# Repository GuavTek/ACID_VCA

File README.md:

Schematic and PCB renders can be found on [CADLAB.io](https://cadlab.io/project/29056/main/files)

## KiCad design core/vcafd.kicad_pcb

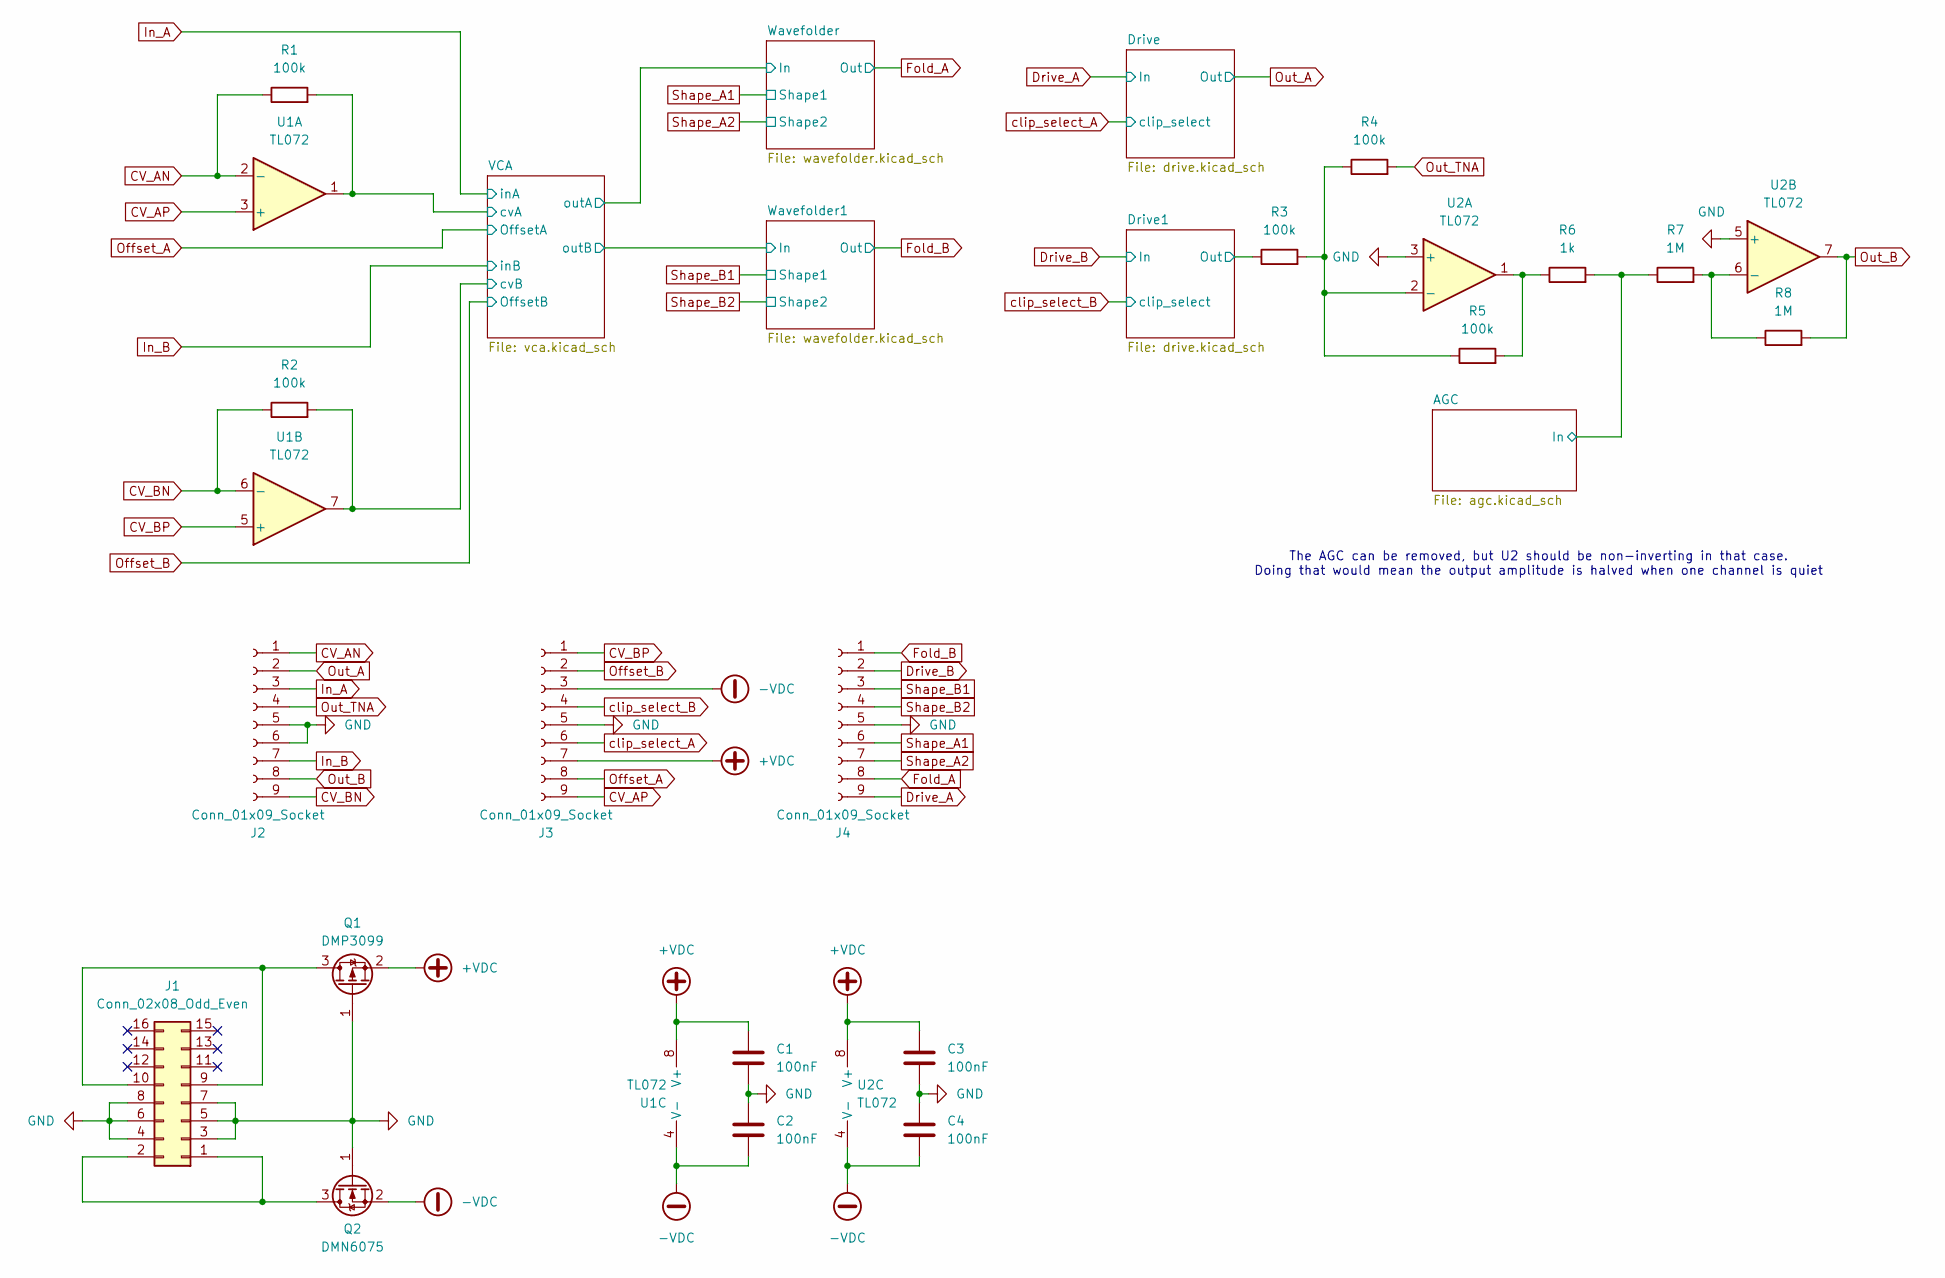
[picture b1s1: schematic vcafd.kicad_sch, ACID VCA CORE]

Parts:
C1, C2, C3, C4: 100nF; C_0603_1608Metric
J1: Conn_02x08_Odd_Even; Header_2x8_Shrouded_SMD
J2, J3, J4: Conn_01x09_Socket; PinSocket_1x09_P2.54mm_Vertical_SMD_Pin1Left
Q1: DMP3099; SOT-23
Q2: DMN6075; SOT-23
R1, R2, R3, R4, R5: 100k; R_0603_1608Metric
R6: 1k; R_0603_1608Metric
R7, R8: 1M; R_0603_1608Metric
U1, U2: TL072; SO-8_3.9x4.9mm_P1.27mm

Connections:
+VDC: C1.1, C3.1, J3.7, Q1.2 (S), U1.8 (V+), U2.8 (V+); also elsewhere on the board
-VDC: C2.2, C4.2, J3.3, Q2.2 (S), U1.4 (V-), U2.4 (V-); also elsewhere on the board
/AGC/In: R6.2, R7.1; also elsewhere on the board
/Drive1/Out: R3.1; also elsewhere on the board
/VCA/cvA: R1.2, U1.1; also elsewhere on the board
/VCA/cvB: R2.2, U1.7; also elsewhere on the board
CV_AN: J2.1, R1.1, U1.2 (-)
CV_AP: J3.9, U1.3 (+)
CV_BN: J2.9, R2.1, U1.6 (-)
CV_BP: J3.1, U1.5 (+)
Drive_A: J4.9; also elsewhere on the board
Drive_B: J4.2; also elsewhere on the board
Fold_A: J4.8; also elsewhere on the board
Fold_B: J4.1; also elsewhere on the board
GND: C1.2, C2.1, C3.2, C4.1, J1.3, J1.4, J1.5, J1.6, J1.7, J1.8, J2.5, J2.6, J3.5, J4.5, Q1.1 (G), Q2.1 (G), U2.3 (+), U2.5 (+); also elsewhere on the board
In_A: J2.3; also elsewhere on the board
In_B: J2.7; also elsewhere on the board
unnamed: J1.1, J1.2, Q2.3 (D)
unnamed: J1.9, J1.10, Q1.3 (D)
unnamed: R5.2, R6.1, U2.1
unnamed: R3.2, R4.1, R5.1, U2.2 (-)
unnamed: R7.2, R8.1, U2.6 (-)
Offset_A: J3.8; also elsewhere on the board
Offset_B: J3.2; also elsewhere on the board
Out_A: J2.2; also elsewhere on the board
Out_B: J2.8, R8.2, U2.7
Out_TNA: J2.4, R4.2
Shape_A1: J4.6; also elsewhere on the board
Shape_A2: J4.7; also elsewhere on the board
Shape_B1: J4.3; also elsewhere on the board
Shape_B2: J4.4; also elsewhere on the board
clip_select_A: J3.6; also elsewhere on the board
clip_select_B: J3.4; also elsewhere on the board

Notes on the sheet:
The AGC can be removed, but U2 should be non-inverting in that case. Doing that would mean the output amplitude is halved when one channel is quiet

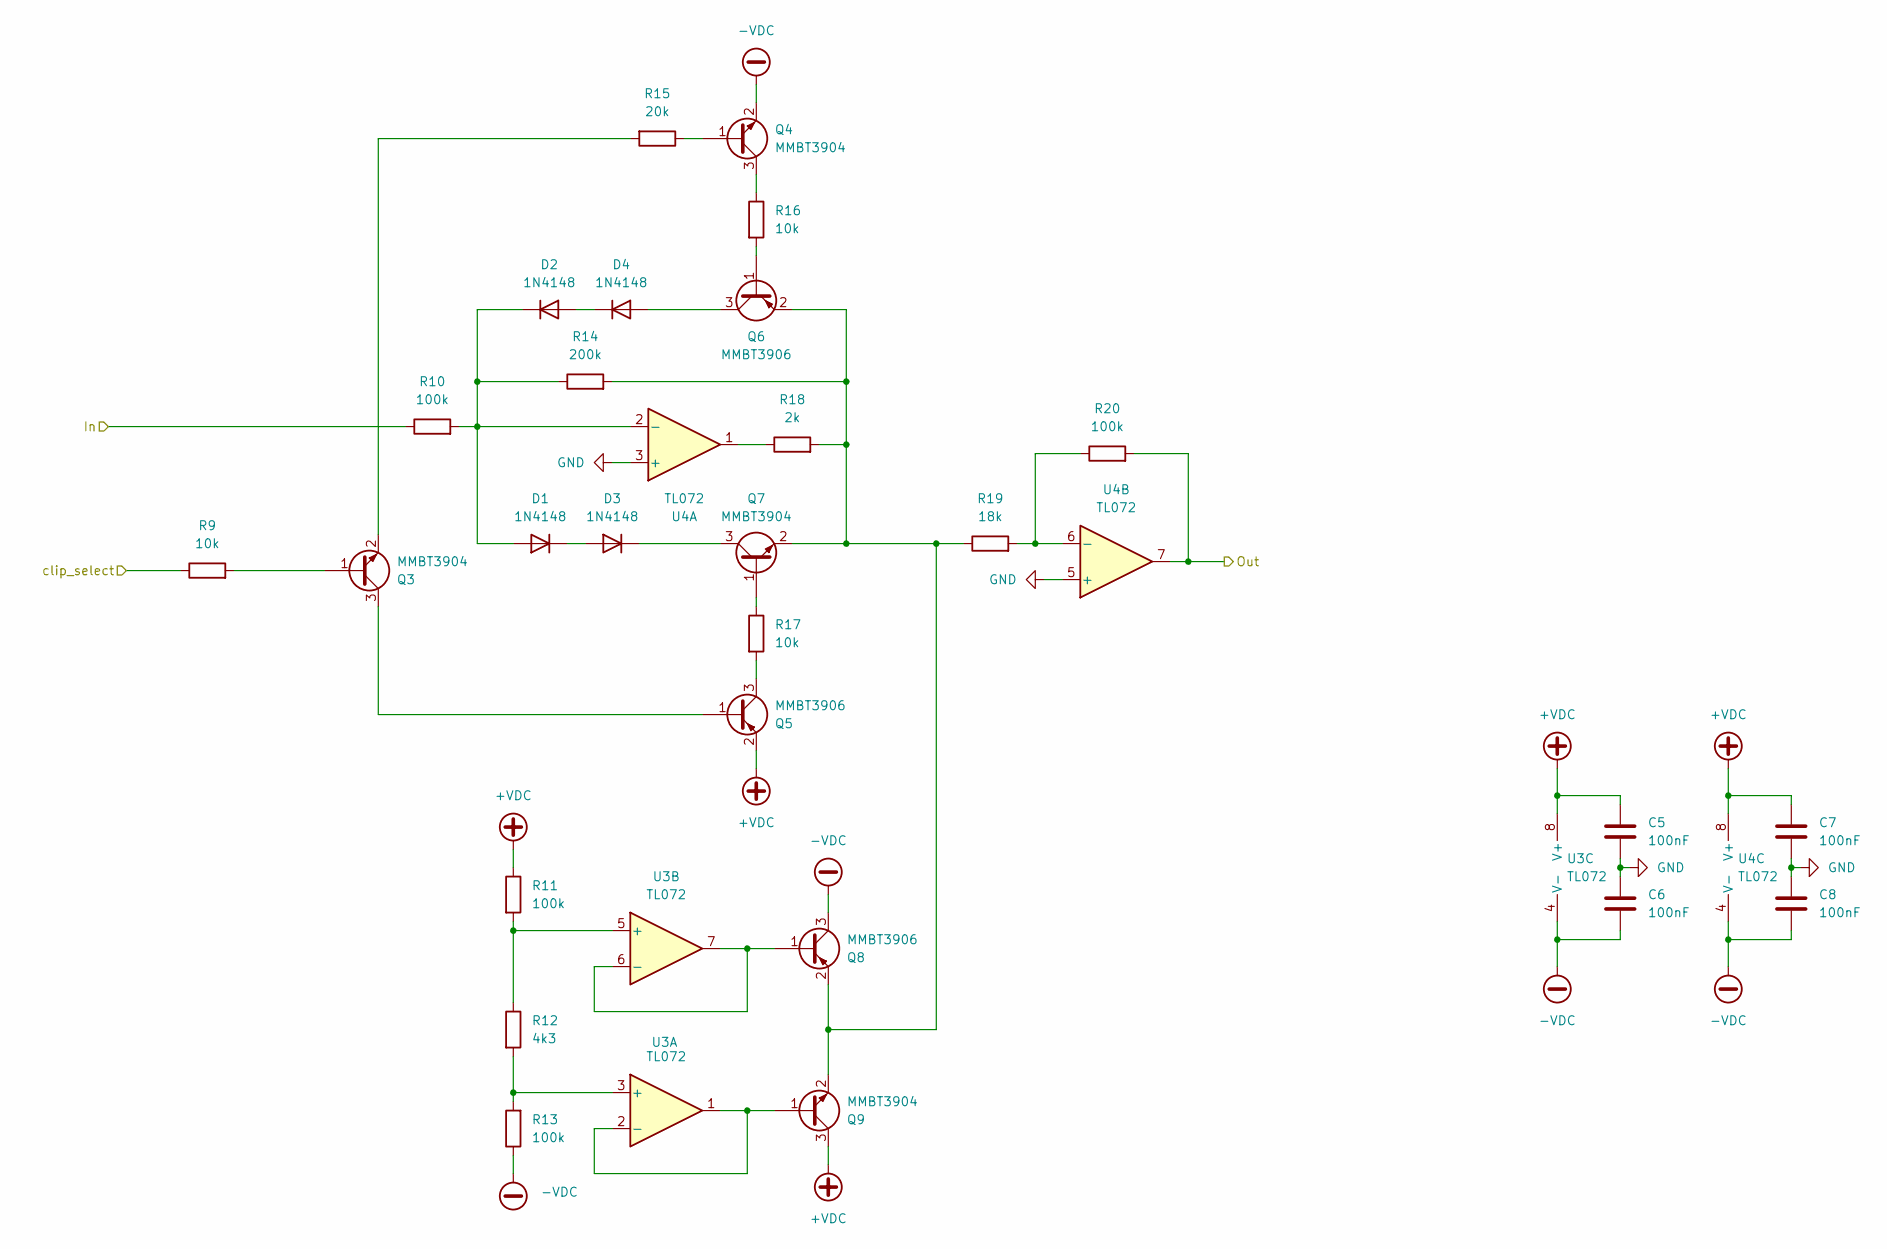
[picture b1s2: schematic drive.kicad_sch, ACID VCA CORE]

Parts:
C5, C6, C7, C8: 100nF; C_0603_1608Metric
D1, D2, D3, D4: 1N4148; D_SOD-323_HandSoldering
Q3, Q4, Q7, Q9: MMBT3904; SOT-23
Q5, Q6, Q8: MMBT3906; SOT-23
R9, R16, R17: 10k; R_0603_1608Metric
R10, R11, R13, R20: 100k; R_0603_1608Metric
R12: 4k3; R_0603_1608Metric
R14: 200k; R_0603_1608Metric
R15: 20k; R_0603_1608Metric
R18: 2k; R_0603_1608Metric
R19: 18k; R_0603_1608Metric
U3, U4: TL072; SO-8_3.9x4.9mm_P1.27mm

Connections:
+VDC: C5.1, C7.1, Q5.2 (E), Q9.3 (C), R11.1, U3.8 (V+), U4.8 (V+); also elsewhere on the board
-VDC: C6.2, C8.2, Q4.2 (E), Q8.3 (C), R13.1, U3.4 (V-), U4.4 (V-); also elsewhere on the board
/Drive1/Out: R20.2, U4.7; also elsewhere on the board
Drive_B: R10.1; also elsewhere on the board
GND: C5.2, C6.1, C7.2, C8.1, U4.3 (+), U4.5 (+); also elsewhere on the board
unnamed: D1.2 (A), D2.1 (K), R10.2, R14.1, U4.2 (-)
unnamed: D1.1 (K), D3.2 (A)
unnamed: D2.2 (A), D4.1 (K)
unnamed: D3.1 (K), Q7.3 (C)
unnamed: D4.2 (A), Q6.3 (C)
unnamed: Q3.1 (B), R9.2
unnamed: Q3.3 (C), Q5.1 (B)
unnamed: Q3.2 (E), R15.2
unnamed: Q4.1 (B), R15.1
unnamed: Q4.3 (C), R16.1
unnamed: Q5.3 (C), R17.2
unnamed: Q6.1 (B), R16.2
unnamed: Q6.2 (E), Q7.2 (E), Q8.2 (E), Q9.2 (E), R14.2, R18.2, R19.1
unnamed: Q7.1 (B), R17.1
unnamed: Q8.1 (B), U3.6 (-), U3.7
unnamed: Q9.1 (B), U3.1, U3.2 (-)
unnamed: R18.1, U4.1
unnamed: R12.2, R13.2, U3.3 (+)
unnamed: R11.2, R12.1, U3.5 (+)
unnamed: R19.2, R20.1, U4.6 (-)
clip_select_B: R9.1; also elsewhere on the board

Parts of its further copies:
C16, C17, C18, C19: 100nF; C_0603_1608Metric
D31, D32, D33, D34: 1N4148; D_SOD-323_HandSoldering
Q12, Q13, Q16, Q18: MMBT3904; SOT-23
Q14, Q15, Q17: MMBT3906; SOT-23
R55, R62, R63: 10k; R_0603_1608Metric
R56, R57, R59, R66: 100k; R_0603_1608Metric
R58: 4k3; R_0603_1608Metric
R60: 200k; R_0603_1608Metric
R61: 20k; R_0603_1608Metric
R64: 2k; R_0603_1608Metric
R65: 18k; R_0603_1608Metric
U8, U9: TL072; SO-8_3.9x4.9mm_P1.27mm

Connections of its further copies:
+VDC: C16.1, C18.1, Q14.2 (E), Q18.3 (C), R57.1, U8.8 (V+), U9.8 (V+); also elsewhere on the board
-VDC: C17.2, C19.2, Q13.2 (E), Q17.3 (C), R59.1, U8.4 (V-), U9.4 (V-); also elsewhere on the board
Drive_A: R56.1; also elsewhere on the board
GND: C16.2, C17.1, C18.2, C19.1, U9.3 (+), U9.5 (+); also elsewhere on the board
unnamed: D31.2 (A), D32.1 (K), R56.2, R60.1, U9.2 (-)
unnamed: D31.1 (K), D33.2 (A)
unnamed: D32.2 (A), D34.1 (K)
unnamed: D33.1 (K), Q16.3 (C)
unnamed: D34.2 (A), Q15.3 (C)
unnamed: Q12.1 (B), R55.2
unnamed: Q12.3 (C), Q14.1 (B)
unnamed: Q12.2 (E), R61.2
unnamed: Q13.1 (B), R61.1
unnamed: Q13.3 (C), R62.1
unnamed: Q14.3 (C), R63.2
unnamed: Q15.1 (B), R62.2
unnamed: Q15.2 (E), Q16.2 (E), Q17.2 (E), Q18.2 (E), R60.2, R64.2, R65.1
unnamed: Q16.1 (B), R63.1
unnamed: Q17.1 (B), U8.6 (-), U8.7
unnamed: Q18.1 (B), U8.1, U8.2 (-)
unnamed: R64.1, U9.1
unnamed: R58.2, R59.2, U8.3 (+)
unnamed: R57.2, R58.1, U8.5 (+)
unnamed: R65.2, R66.1, U9.6 (-)
Out_A: R66.2, U9.7; also elsewhere on the board
clip_select_A: R55.1; also elsewhere on the board

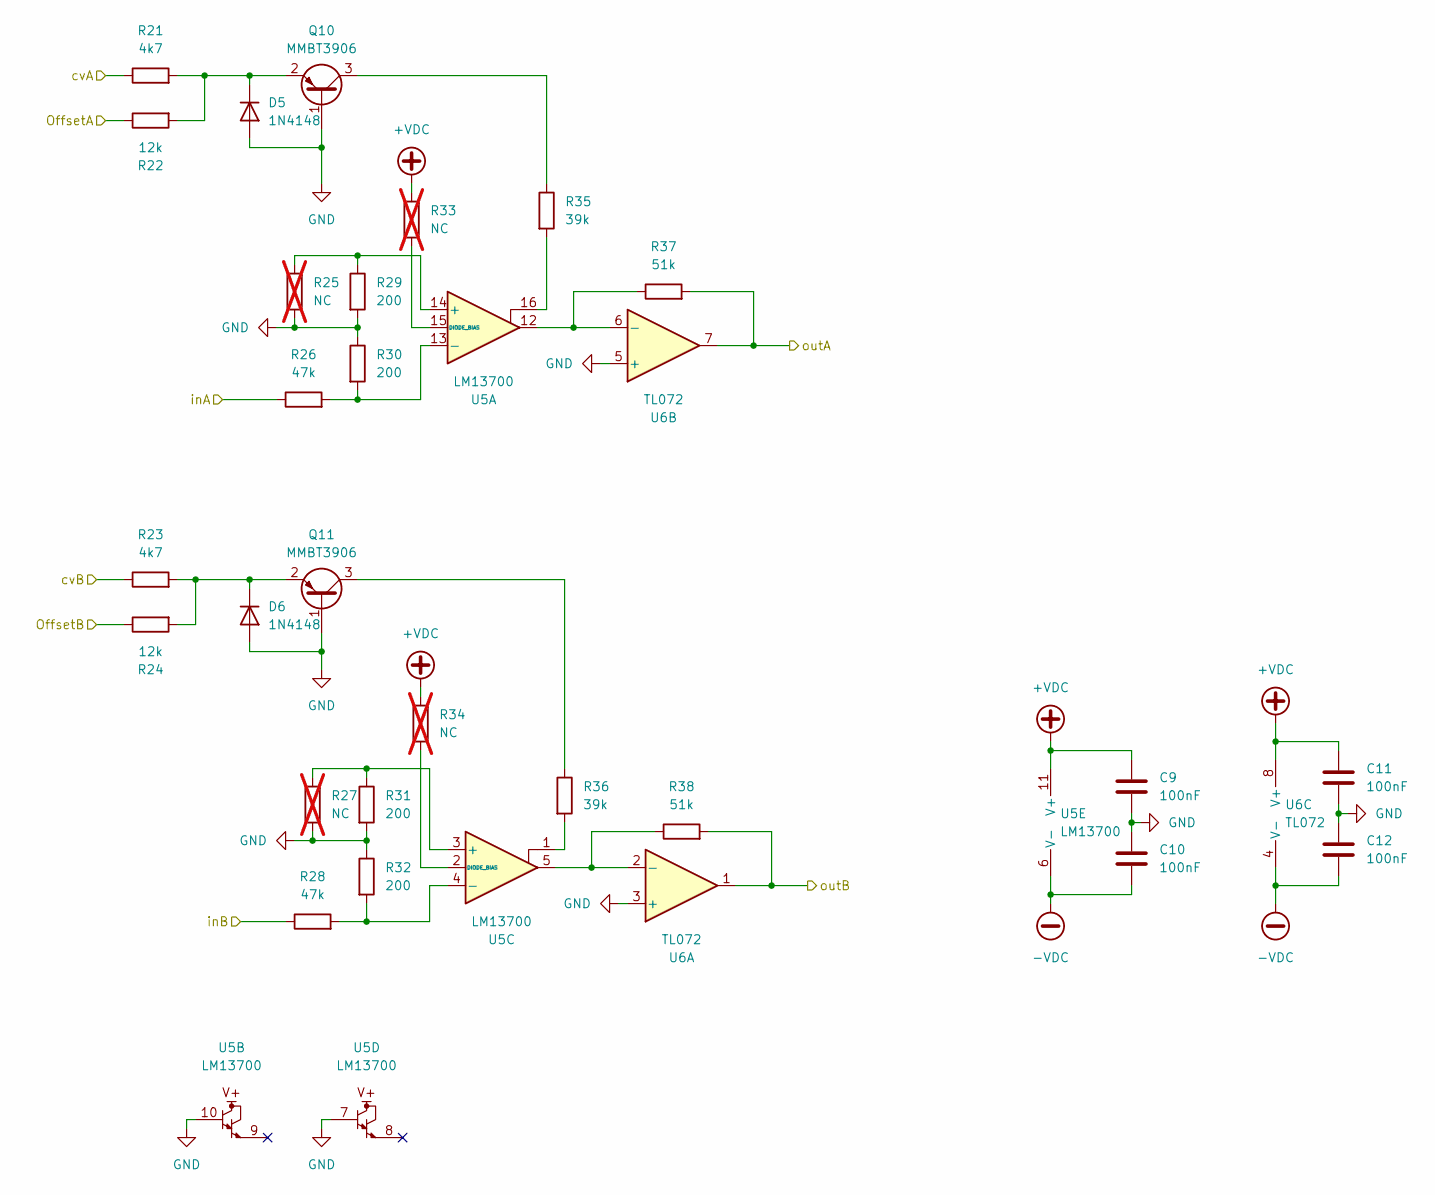
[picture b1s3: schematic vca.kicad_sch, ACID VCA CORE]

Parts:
C9, C10, C11, C12: 100nF; C_0603_1608Metric
D5, D6: 1N4148; D_SOD-323_HandSoldering
Q10, Q11: MMBT3906; SOT-23
R21, R23: 4k7; R_0603_1608Metric
R22, R24: 12k; R_0603_1608Metric
R25, R27, R33, R34: NC; R_0603_1608Metric; not fitted
R26, R28: 47k; R_0603_1608Metric
R29, R30, R31, R32: 200; R_0603_1608Metric
R35, R36: 39k; R_0603_1608Metric
R37, R38: 51k; R_0603_1608Metric
U5: LM13700; SO-16_3.9x9.9mm_P1.27mm
U6: TL072; SO-8_3.9x4.9mm_P1.27mm

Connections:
+VDC: C9.1, C11.1, R33.1, R34.1, U5.11 (V+), U6.8 (V+); also elsewhere on the board
-VDC: C10.2, C12.2, U5.6 (V-), U6.4 (V-); also elsewhere on the board
/VCA/cvA: R21.1; also elsewhere on the board
/VCA/cvB: R23.1; also elsewhere on the board
/VCA/outA: R37.2, U6.7; also elsewhere on the board
/VCA/outB: R38.2, U6.1; also elsewhere on the board
GND: C9.2, C10.1, C11.2, C12.1, D5.2 (A), D6.2 (A), Q10.1 (B), Q11.1 (B), R25.2, R27.2, R29.2, R30.1, R31.2, R32.1, U5.7, U5.10, U6.3 (+), U6.5 (+); also elsewhere on the board
In_A: R26.1; also elsewhere on the board
In_B: R28.1; also elsewhere on the board
unnamed: D5.1 (K), Q10.2 (E), R21.2, R22.2
unnamed: D6.1 (K), Q11.2 (E), R23.2, R24.2
unnamed: Q10.3 (C), R35.1
unnamed: Q11.3 (C), R36.1
unnamed: R35.2, U5.16
unnamed: R36.2, U5.1
unnamed: R25.1, R29.1, U5.14 (+)
unnamed: R26.2, R30.2, U5.13 (-)
unnamed: R33.2, U5.15 (DIODE_BIAS)
unnamed: R27.1, R31.1, U5.3 (+)
unnamed: R28.2, R32.2, U5.4 (-)
unnamed: R34.2, U5.2 (DIODE_BIAS)
unnamed: R38.1, U5.5, U6.2 (-)
unnamed: R37.1, U5.12, U6.6 (-)
Offset_A: R22.1; also elsewhere on the board
Offset_B: R24.1; also elsewhere on the board

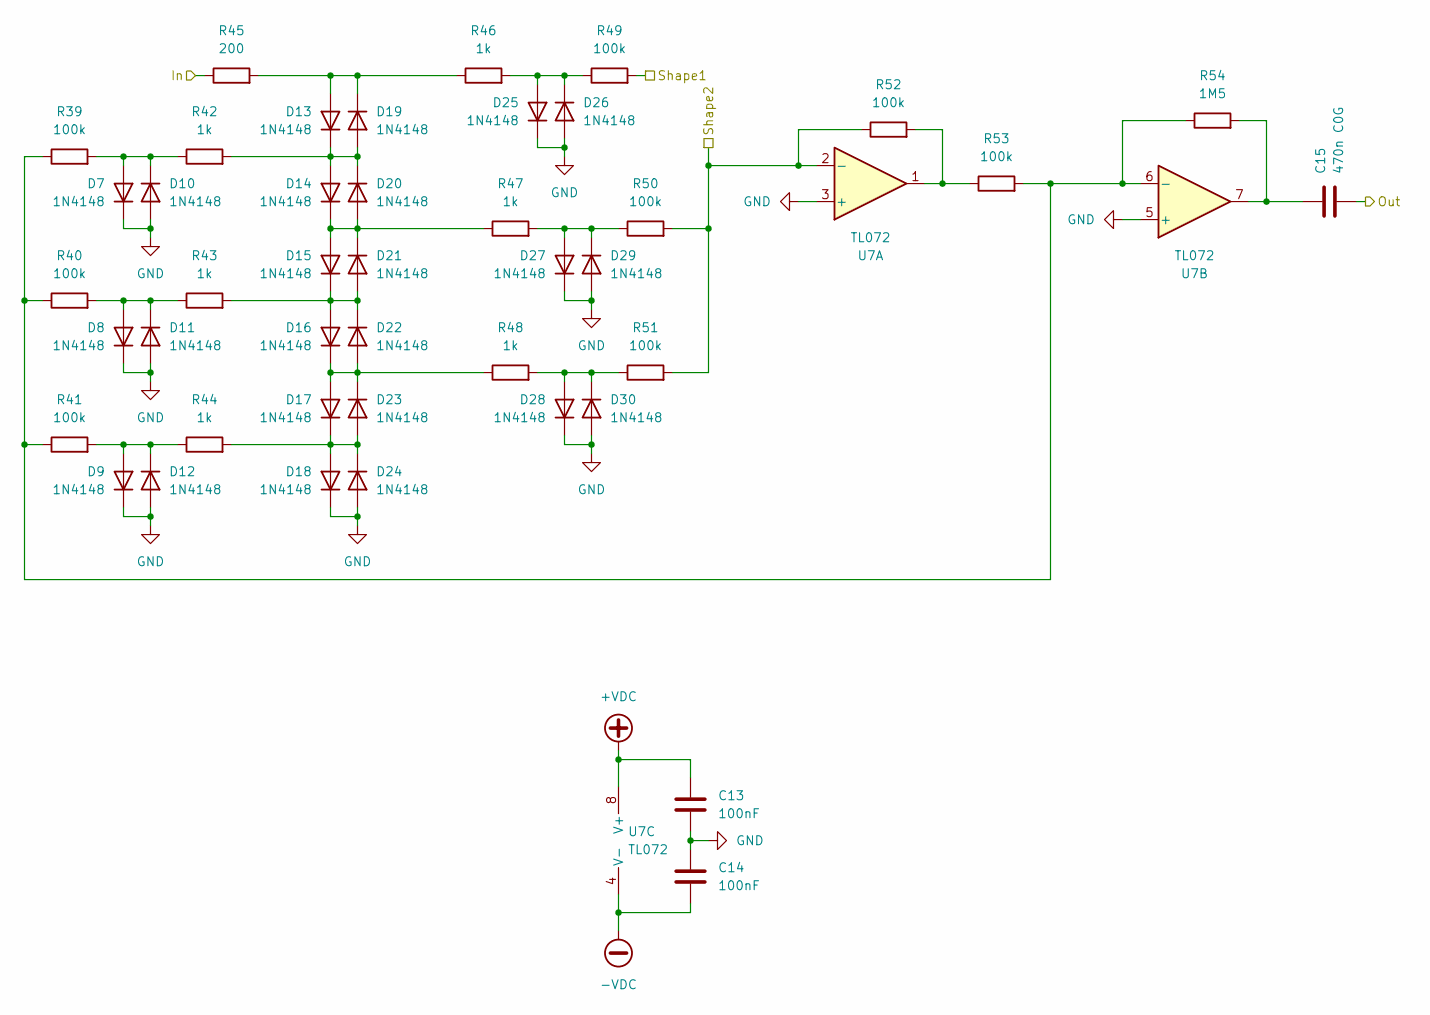
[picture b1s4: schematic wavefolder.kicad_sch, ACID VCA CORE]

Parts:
C13, C14: 100nF; C_0603_1608Metric
C15: 470n C0G; C_1206_3216Metric
D7, D8, D9, D10, D11, D12, D13, D14, D15, D16, D17, D18, D19, D20, D21, D22, D23, D24, D25, D26, D27, D28, D29, D30: 1N4148; D_SOD-323_HandSoldering
R39, R40, R41, R49, R50, R51, R52, R53: 100k; R_0603_1608Metric
R42, R43, R44, R46, R47, R48: 1k; R_0603_1608Metric
R45: 200; R_0603_1608Metric
R54: 1M5; R_0603_1608Metric
U7: TL072; SO-8_3.9x4.9mm_P1.27mm

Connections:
+VDC: C13.1, U7.8 (V+); also elsewhere on the board
-VDC: C14.2, U7.4 (V-); also elsewhere on the board
/VCA/outA: R45.1; also elsewhere on the board
Fold_A: C15.2; also elsewhere on the board
GND: C13.2, C14.1, D7.1 (K), D8.1 (K), D9.1 (K), D10.2 (A), D11.2 (A), D12.2 (A), D18.1 (K), D24.2 (A), D25.1 (K), D26.2 (A), D27.1 (K), D28.1 (K), D29.2 (A), D30.2 (A), U7.3 (+), U7.5 (+); also elsewhere on the board
unnamed: C15.1, R54.2, U7.7
unnamed: D7.2 (A), D10.1 (K), R39.2, R42.1
unnamed: D8.2 (A), D11.1 (K), R40.2, R43.1
unnamed: D9.2 (A), D12.1 (K), R41.2, R44.1
unnamed: D13.2 (A), D19.1 (K), R45.2, R46.1
unnamed: D13.1 (K), D14.2 (A), D19.2 (A), D20.1 (K), R42.2
unnamed: D14.1 (K), D15.2 (A), D20.2 (A), D21.1 (K), R47.1
unnamed: D15.1 (K), D16.2 (A), D21.2 (A), D22.1 (K), R43.2
unnamed: D16.1 (K), D17.2 (A), D22.2 (A), D23.1 (K), R48.1
unnamed: D17.1 (K), D18.2 (A), D23.2 (A), D24.1 (K), R44.2
unnamed: D25.2 (A), D26.1 (K), R46.2, R49.1
unnamed: D27.2 (A), D29.1 (K), R47.2, R50.1
unnamed: D28.2 (A), D30.1 (K), R48.2, R51.1
unnamed: R52.2, R53.1, U7.1
unnamed: R39.1, R40.1, R41.1, R53.2, R54.1, U7.6 (-)
Shape_A1: R49.2; also elsewhere on the board
Shape_A2: R50.2, R51.2, R52.1, U7.2 (-); also elsewhere on the board

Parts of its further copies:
C20, C21: 100nF; C_0603_1608Metric
C22: 470n C0G; C_1206_3216Metric
D35, D36, D37, D38, D39, D40, D41, D42, D43, D44, D45, D46, D47, D48, D49, D50, D51, D52, D53, D54, D55, D56, D57, D58: 1N4148; D_SOD-323_HandSoldering
R67, R68, R69, R77, R78, R79, R80, R81: 100k; R_0603_1608Metric
R70, R71, R72, R74, R75, R76: 1k; R_0603_1608Metric
R73: 200; R_0603_1608Metric
R82: 1M5; R_0603_1608Metric
U10: TL072; SO-8_3.9x4.9mm_P1.27mm

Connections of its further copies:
+VDC: C20.1, U10.8 (V+); also elsewhere on the board
-VDC: C21.2, U10.4 (V-); also elsewhere on the board
/VCA/outB: R73.1; also elsewhere on the board
Fold_B: C22.2; also elsewhere on the board
GND: C20.2, C21.1, D35.1 (K), D36.1 (K), D37.1 (K), D38.2 (A), D39.2 (A), D40.2 (A), D46.1 (K), D52.2 (A), D53.1 (K), D54.2 (A), D55.1 (K), D56.1 (K), D57.2 (A), D58.2 (A), U10.3 (+), U10.5 (+); also elsewhere on the board
unnamed: C22.1, R82.2, U10.7
unnamed: D35.2 (A), D38.1 (K), R67.2, R70.1
unnamed: D36.2 (A), D39.1 (K), R68.2, R71.1
unnamed: D37.2 (A), D40.1 (K), R69.2, R72.1
unnamed: D41.2 (A), D47.1 (K), R73.2, R74.1
unnamed: D41.1 (K), D42.2 (A), D47.2 (A), D48.1 (K), R70.2
unnamed: D42.1 (K), D43.2 (A), D48.2 (A), D49.1 (K), R75.1
unnamed: D43.1 (K), D44.2 (A), D49.2 (A), D50.1 (K), R71.2
unnamed: D44.1 (K), D45.2 (A), D50.2 (A), D51.1 (K), R76.1
unnamed: D45.1 (K), D46.2 (A), D51.2 (A), D52.1 (K), R72.2
unnamed: D53.2 (A), D54.1 (K), R74.2, R77.1
unnamed: D55.2 (A), D57.1 (K), R75.2, R78.1
unnamed: D56.2 (A), D58.1 (K), R76.2, R79.1
unnamed: R80.2, R81.1, U10.1
unnamed: R67.1, R68.1, R69.1, R81.2, R82.1, U10.6 (-)
Shape_B1: R77.2; also elsewhere on the board
Shape_B2: R78.2, R79.2, R80.1, U10.2 (-); also elsewhere on the board

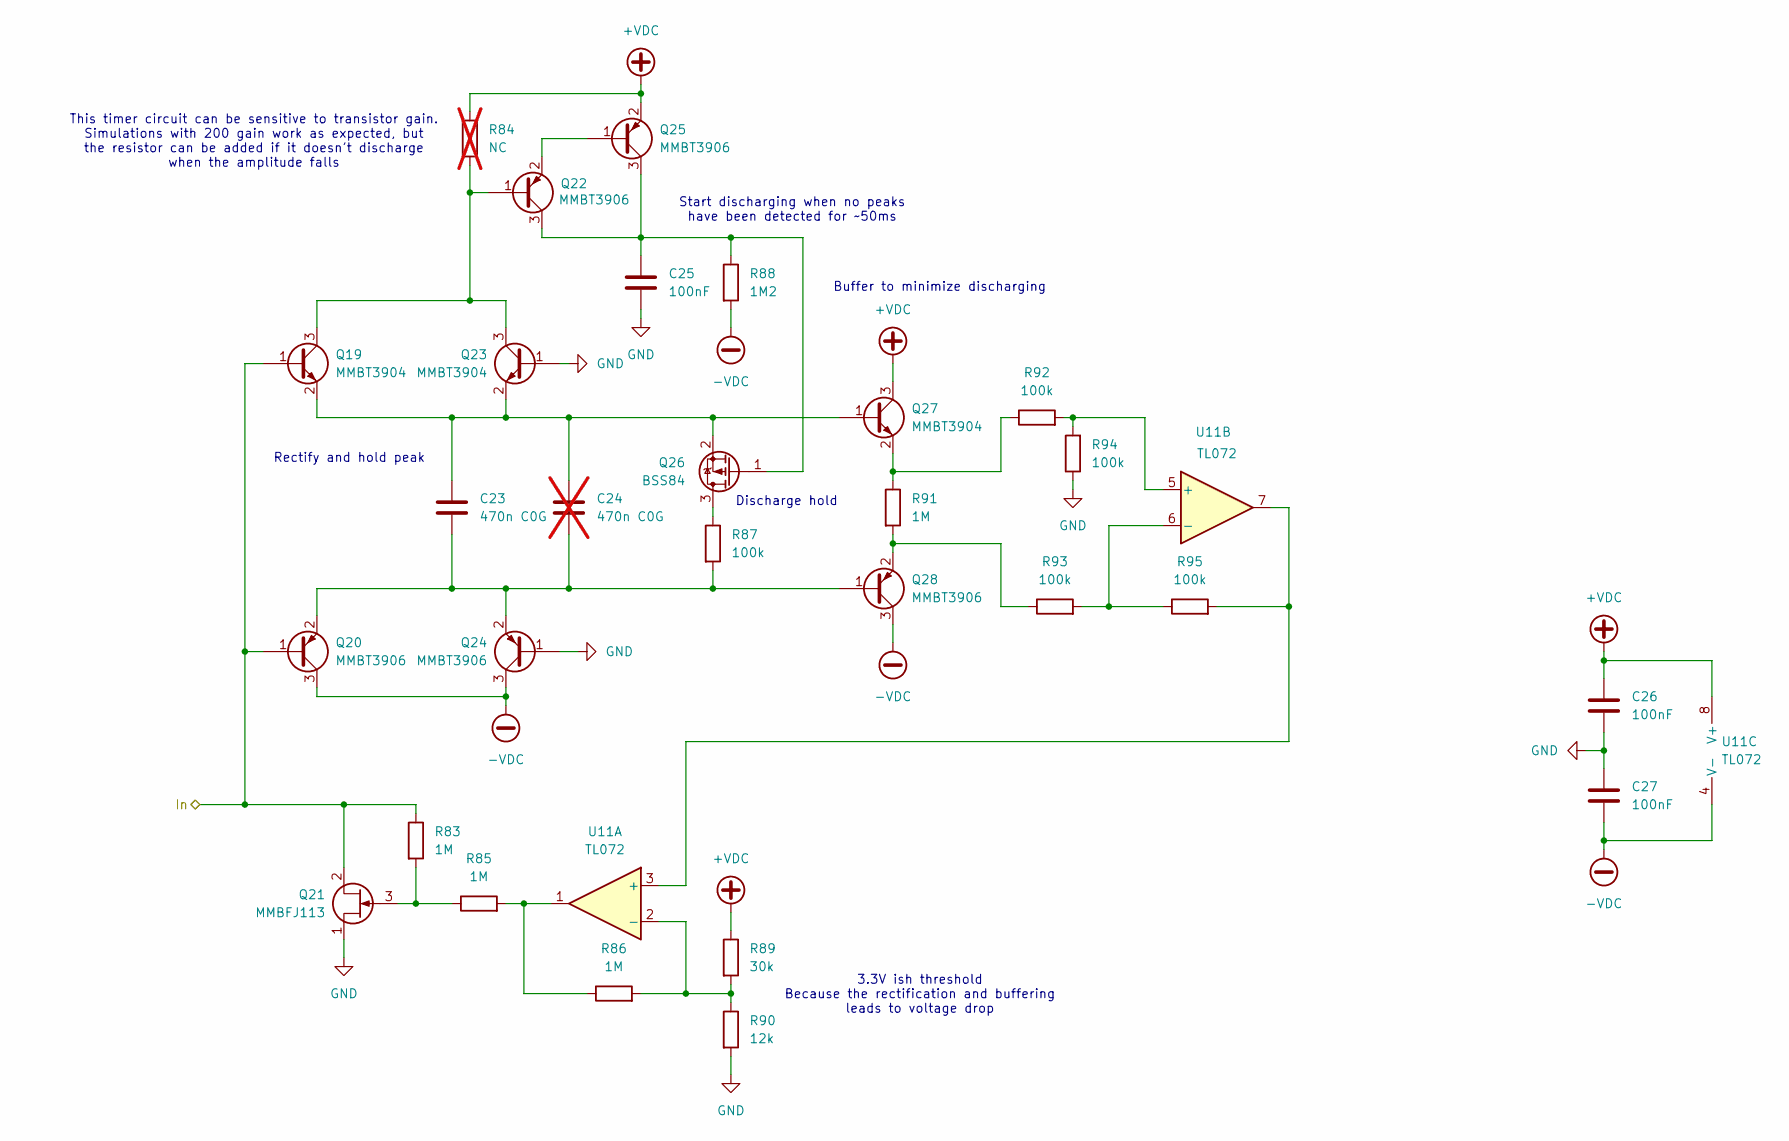
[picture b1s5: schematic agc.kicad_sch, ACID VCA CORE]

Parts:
C23: 470n C0G; C_1206_3216Metric
C24: 470n C0G; C_1206_3216Metric; not fitted
C25, C26, C27: 100nF; C_0603_1608Metric
Q19, Q23, Q27: MMBT3904; SOT-23
Q20, Q22, Q24, Q25, Q28: MMBT3906; SOT-23
Q21: MMBFJ113; SOT-23
Q26: BSS84; SOT-23
R83, R85, R86, R91: 1M; R_0603_1608Metric
R84: NC; R_0603_1608Metric; not fitted
R87, R92, R93, R94, R95: 100k; R_0603_1608Metric
R88: 1M2; R_0603_1608Metric
R89: 30k; R_0603_1608Metric
R90: 12k; R_0603_1608Metric
U11: TL072; SO-8_3.9x4.9mm_P1.27mm

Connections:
+VDC: C26.1, Q25.2 (E), Q27.3 (C), R84.1, R89.1, U11.8 (V+); also elsewhere on the board
-VDC: C27.2, Q20.3 (C), Q24.3 (C), Q28.3 (C), R88.2, U11.4 (V-); also elsewhere on the board
/AGC/In: Q19.1 (B), Q20.1 (B), Q21.2 (S), R83.1; also elsewhere on the board
GND: C25.2, C26.2, C27.1, Q21.1 (D), Q23.1 (B), Q24.1 (B), R90.2, R94.1; also elsewhere on the board
unnamed: Q19.3 (C), Q22.1 (B), Q23.3 (C), R84.2
unnamed: C23.1, C24.1, Q19.2 (E), Q23.2 (E), Q26.2 (S), Q27.1 (B)
unnamed: C23.2, C24.2, Q20.2 (E), Q24.2 (E), Q28.1 (B), R87.2
unnamed: Q21.3 (G), R83.2, R85.1
unnamed: C25.1, Q22.3 (C), Q25.3 (C), Q26.1 (G), R88.1
unnamed: Q22.2 (E), Q25.1 (B)
unnamed: Q26.3 (D), R87.1
unnamed: Q27.2 (E), R91.1, R92.1
unnamed: Q28.2 (E), R91.2, R93.1
unnamed: R85.2, R86.1, U11.1
unnamed: R95.2, U11.3 (+), U11.7
unnamed: R86.2, R89.2, R90.1, U11.2 (-)
unnamed: R92.2, R94.2, U11.5 (+)
unnamed: R93.2, R95.1, U11.6 (-)

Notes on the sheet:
Start discharging when no peaks have been detected for ~50ms
3.3V ish threshold Because the rectification and buffering leads to voltage drop
Buffer to minimize discharging
Rectify and hold peak
Discharge hold
This timer circuit can be sensitive to transistor gain. Simulations with 200 gain work as expected, but the resistor can be added if it doesn't discharge when the amplitude falls

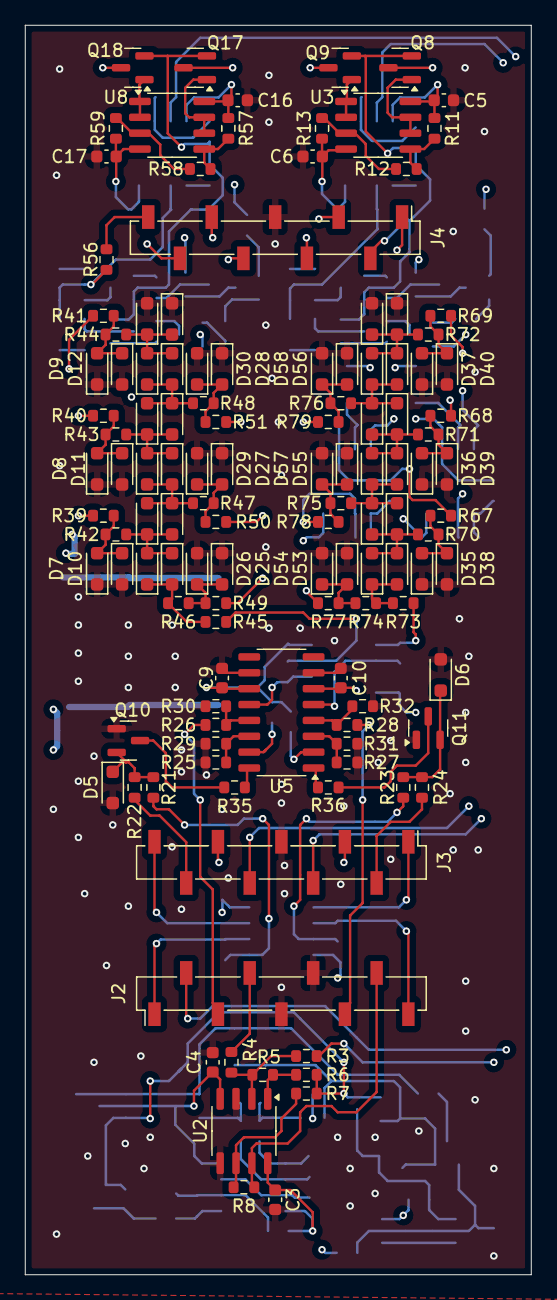
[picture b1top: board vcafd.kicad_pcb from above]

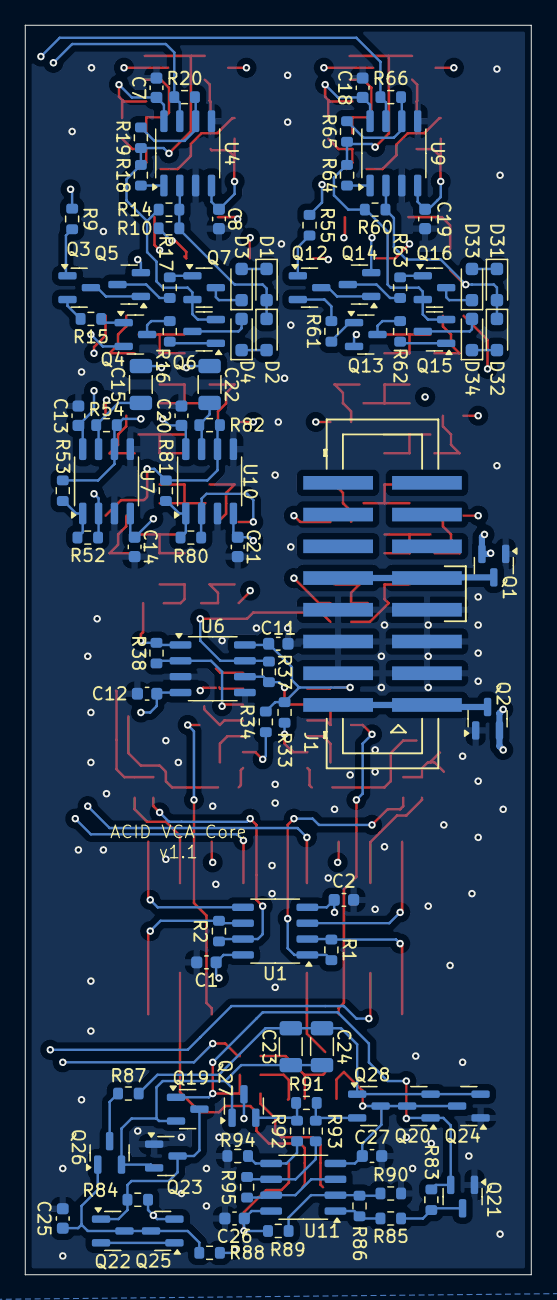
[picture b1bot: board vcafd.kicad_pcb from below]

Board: 4 copper layers, 40.5 x 100.0 mm, 223 parts (99 on the bottom side), 133 nets.

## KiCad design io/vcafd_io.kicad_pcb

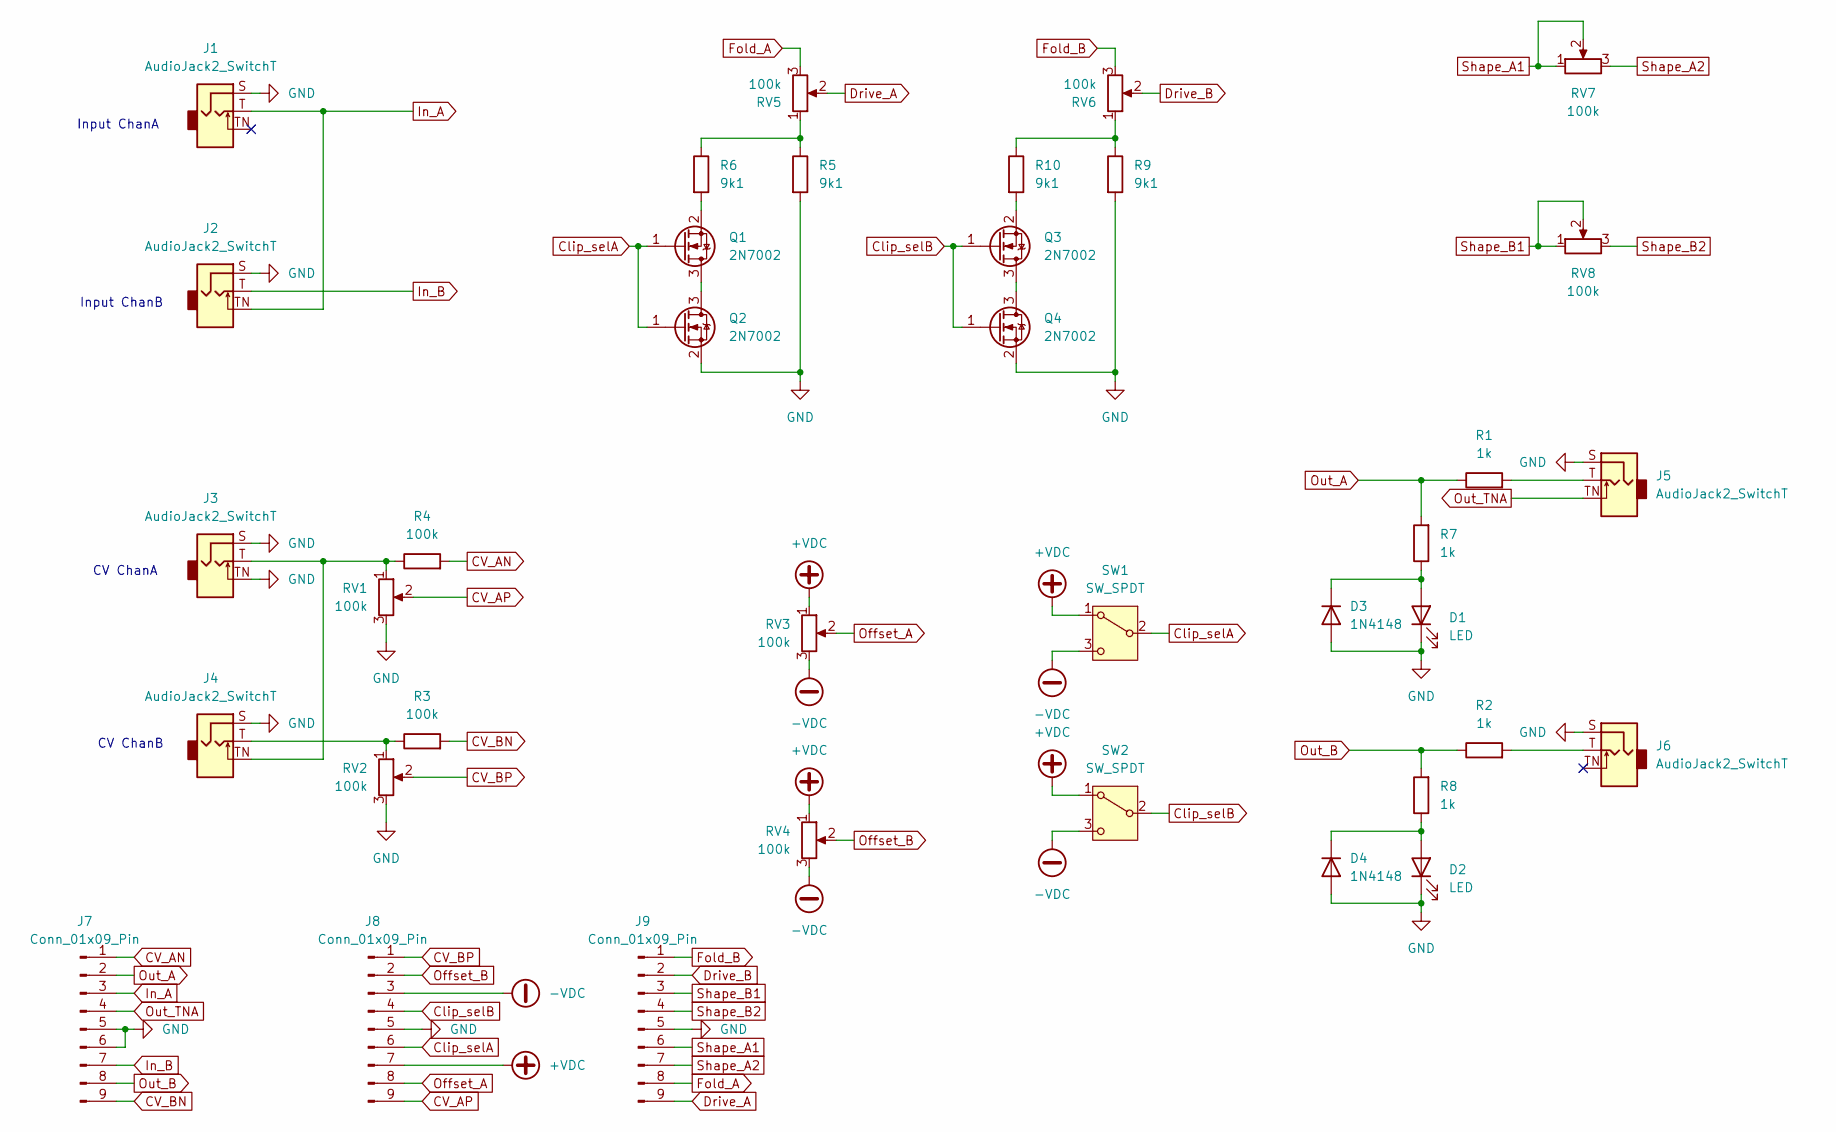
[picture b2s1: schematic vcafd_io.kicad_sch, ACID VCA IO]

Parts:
D1, D2: LED; LED_D3.0mm_Clear
D3, D4: 1N4148; D_SOD-323_HandSoldering
J1, J2, J3, J4, J5, J6: AudioJack2_SwitchT; PJ398SM
J7, J8, J9: Conn_01x09_Pin; PinHeader_1x09_P2.54mm_Vertical_SMD_Pin1Left
Q1, Q2, Q3, Q4: 2N7002; SOT-23
R1, R2, R7, R8: 1k; R_0603_1608Metric
R3, R4: 100k; R_0603_1608Metric
R5, R6, R9, R10: 9k1; R_0603_1608Metric
RV1, RV2, RV3, RV4, RV7, RV8: 100k; Potentiometer_Bourns_PTV09A-1_Single_Vertical
RV5, RV6: 100k; Potentiometer_TT_P0915N
SW1, SW2: SW_SPDT; Toggle switch mini

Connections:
+VDC: J8.7, RV3.1, RV4.1, SW1.1 (A), SW2.1 (A)
-VDC: J8.3, RV3.3, RV4.3, SW1.3 (C), SW2.3 (C)
CV_AN: J7.1, R4.2
CV_AP: J8.9, RV1.2
CV_BN: J7.9, R3.2
CV_BP: J8.1, RV2.2
Clip_selA: J8.6, Q1.1 (G), Q2.1 (G), SW1.2 (B)
Clip_selB: J8.4, Q3.1 (G), Q4.1 (G), SW2.2 (B)
Drive_A: J9.9, RV5.2
Drive_B: J9.2, RV6.2
Fold_A: J9.8, RV5.3
Fold_B: J9.1, RV6.3
GND: D1.1 (K), D2.1 (K), D3.2 (A), D4.2 (A), J1.S, J2.S, J3.S, J3.TN, J4.S, J5.S, J6.S, J7.5, J7.6, J8.5, J9.5, Q2.2 (S), Q4.2 (S), R5.2, R9.2, RV1.3, RV2.3
In_A: J1.T, J2.TN, J7.3
In_B: J2.T, J7.7
unnamed: D1.2 (A), D3.1 (K), R7.1
unnamed: D2.2 (A), D4.1 (K), R8.1
unnamed: J3.T, J4.TN, R4.1, RV1.1
unnamed: J4.T, R3.1, RV2.1
unnamed: J5.T, R1.2
unnamed: J6.T, R2.2
unnamed: Q1.3 (D), Q2.3 (D)
unnamed: Q1.2 (S), R6.2
unnamed: Q3.3 (D), Q4.3 (D)
unnamed: Q3.2 (S), R10.2
unnamed: R5.1, R6.1, RV5.1
unnamed: R9.1, R10.1, RV6.1
Offset_A: J8.8, RV3.2
Offset_B: J8.2, RV4.2
Out_A: J7.2, R1.1, R7.2
Out_B: J7.8, R2.1, R8.2
Out_TNA: J5.TN, J7.4
Shape_A1: J9.6, RV7.1, RV7.2
Shape_A2: J9.7, RV7.3
Shape_B1: J9.3, RV8.1, RV8.2
Shape_B2: J9.4, RV8.3

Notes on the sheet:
CV ChanA
CV ChanB
Input ChanB
Input ChanA
